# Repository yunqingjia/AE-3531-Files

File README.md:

# AE-3531-Files
Class project for the controls analysis course at Georgia Tech.

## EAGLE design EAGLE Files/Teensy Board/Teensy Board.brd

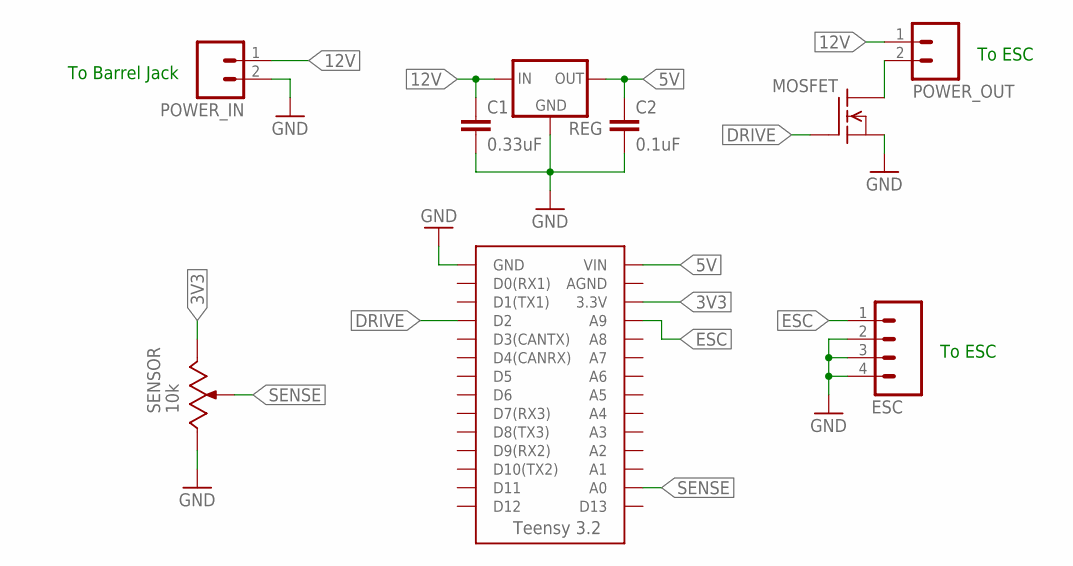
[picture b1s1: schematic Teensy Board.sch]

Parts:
C1: 0.33uF; 0805
C2: 0.1uF; 0805
ESC: M04; 1X04
MOSFET: SI2312; SOT-23
POWER_IN: M02; 1X02
POWER_OUT: M02; 1X02
REG: L78L; SOT-89
SENSOR: 10k; SV03A
U$2: TEENSY_3.2_SIMPLE

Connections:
3V3: SENSOR.1 (E), U$2.3.3V
5V: C2.1, REG.1 (OUT), U$2.VIN
12V: C1.1, POWER_IN.1, POWER_OUT.1, REG.3 (IN)
DRIVE: MOSFET.1 (G), U$2.D2
ESC: ESC.1, U$2.A9
GND: C1.2, C2.2, ESC.2, ESC.3, ESC.4, MOSFET.2 (S), POWER_IN.2, REG.2 (GND), REG.2.1 (GND), REG.2.2 (GND), SENSOR.3 (A), U$2.GND
unnamed: MOSFET.3 (D), POWER_OUT.2
SENSE: SENSOR.2 (S), SENSOR.2.1 (S), U$2.A0

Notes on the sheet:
To Barrel Jack
To ESC

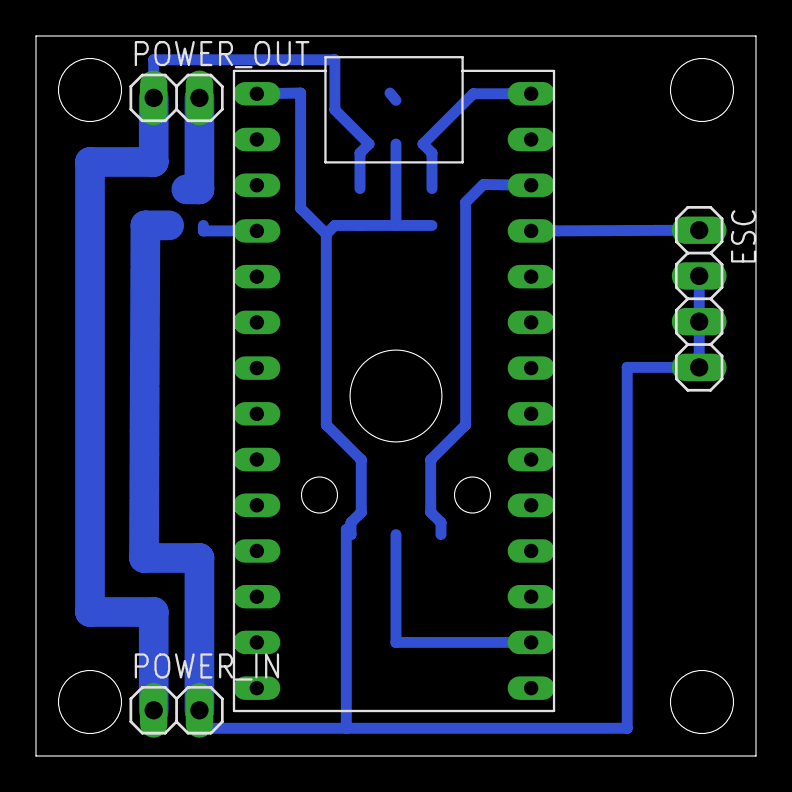
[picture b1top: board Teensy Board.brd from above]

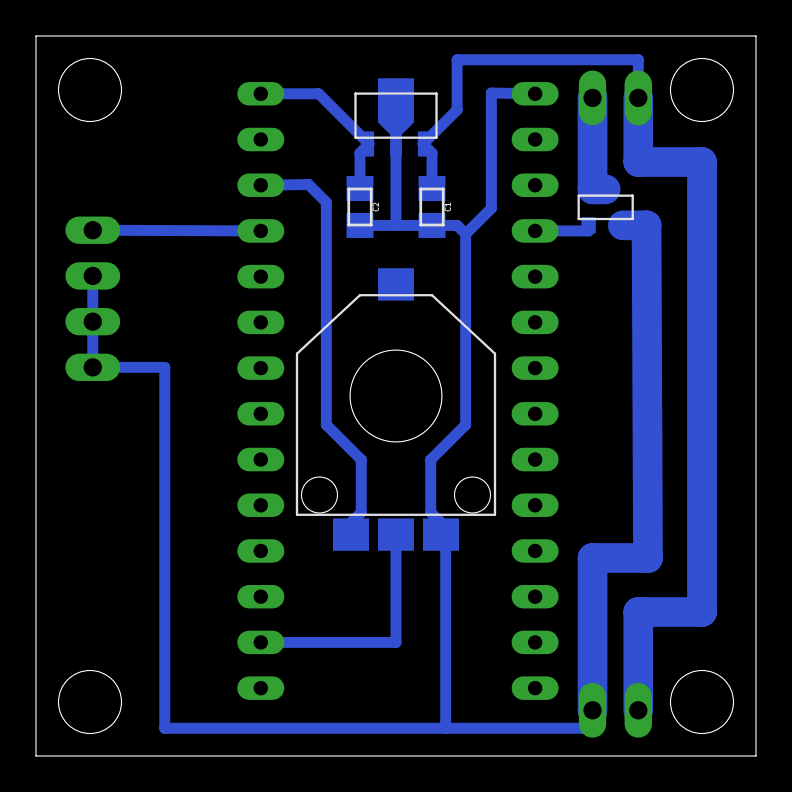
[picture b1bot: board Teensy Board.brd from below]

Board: 2 copper layers, 40.0 x 40.0 mm, 9 parts (5 on the bottom side), 8 nets.

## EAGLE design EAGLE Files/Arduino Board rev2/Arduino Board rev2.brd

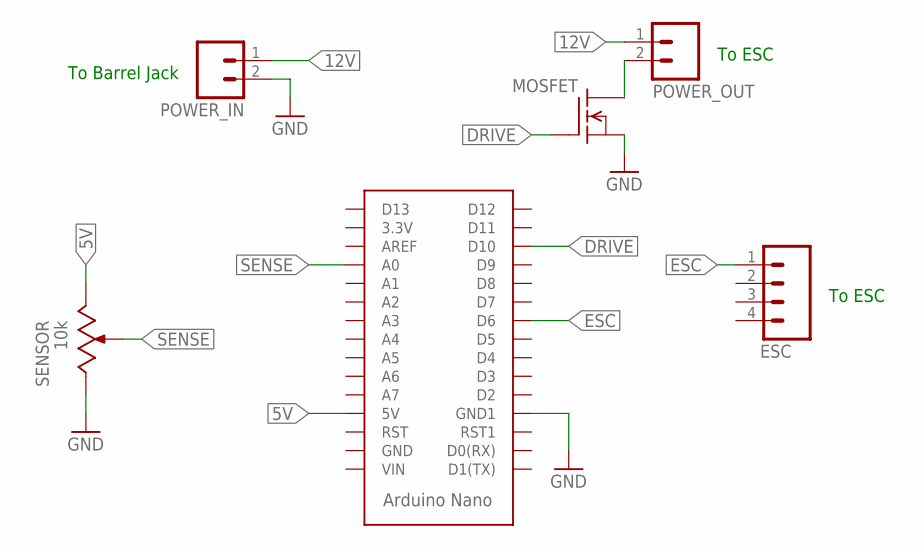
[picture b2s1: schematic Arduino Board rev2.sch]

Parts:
ESC: M04; 1X04
MOSFET: SI2312; SOT-23
POWER_IN: M02; 1X02
POWER_OUT: M02; 1X02
SENSOR: 10k; SV03A
U$1: ARDUINO_NANO

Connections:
5V: SENSOR.3 (A), U$1.5V
12V: POWER_IN.1, POWER_OUT.1
DRIVE: MOSFET.1 (G), U$1.D10
ESC: ESC.1, U$1.D6
GND: MOSFET.2 (S), POWER_IN.2, SENSOR.1 (E), U$1.GND1
unnamed: MOSFET.3 (D), POWER_OUT.2
SENSE: SENSOR.2 (S), SENSOR.2.1 (S), U$1.A0

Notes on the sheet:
To Barrel Jack
To ESC

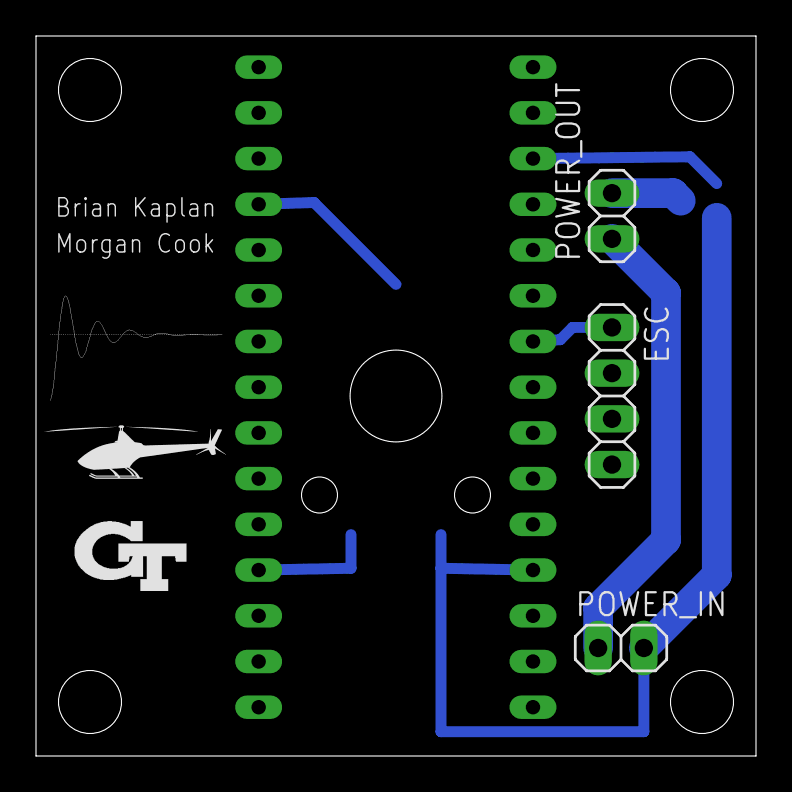
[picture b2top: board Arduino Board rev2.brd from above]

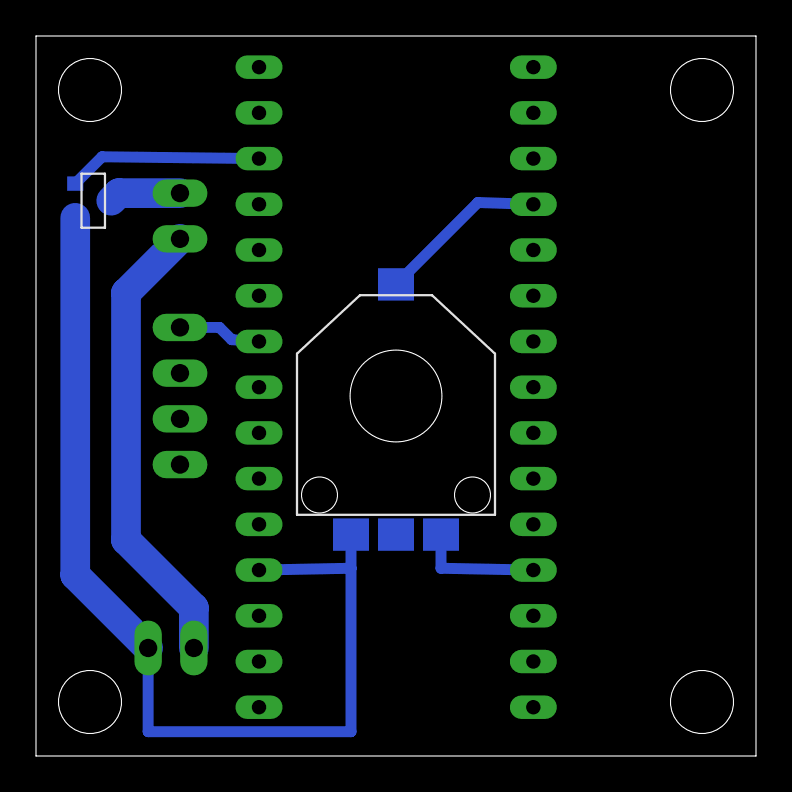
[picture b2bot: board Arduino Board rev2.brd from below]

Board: 2 copper layers, 40.0 x 40.0 mm, 6 parts (2 on the bottom side), 7 nets.

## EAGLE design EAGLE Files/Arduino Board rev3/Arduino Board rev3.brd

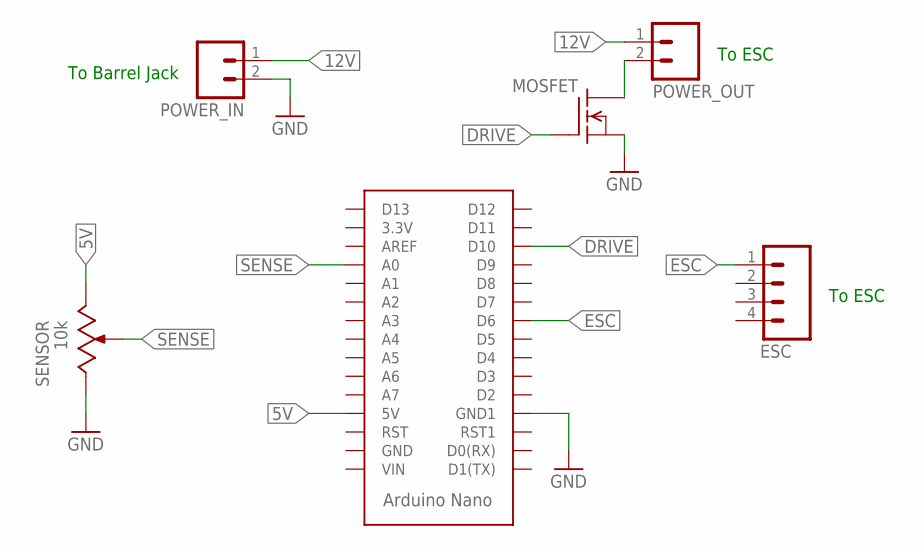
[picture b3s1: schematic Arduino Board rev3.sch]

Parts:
ARDUINO_NANO: ARDUINO_NANO
ESC: M04; 1X04
MOSFET: N-CHANNEL_MOSFETGENERIC; TO-220-SINK
POWER_IN: M02; 1X02
POWER_OUT: M02; 1X02
SENSOR: 10k; SV03A

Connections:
5V: ARDUINO_NANO.5V, SENSOR.3 (A)
12V: POWER_IN.1, POWER_OUT.1
DRIVE: ARDUINO_NANO.D10, MOSFET.1 (G)
ESC: ARDUINO_NANO.D6, ESC.1
GND: ARDUINO_NANO.GND1, MOSFET.3 (S), POWER_IN.2, SENSOR.1 (E)
unnamed: MOSFET.2 (D), POWER_OUT.2
SENSE: ARDUINO_NANO.A0, SENSOR.2 (S), SENSOR.2.1 (S)

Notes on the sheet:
To Barrel Jack
To ESC

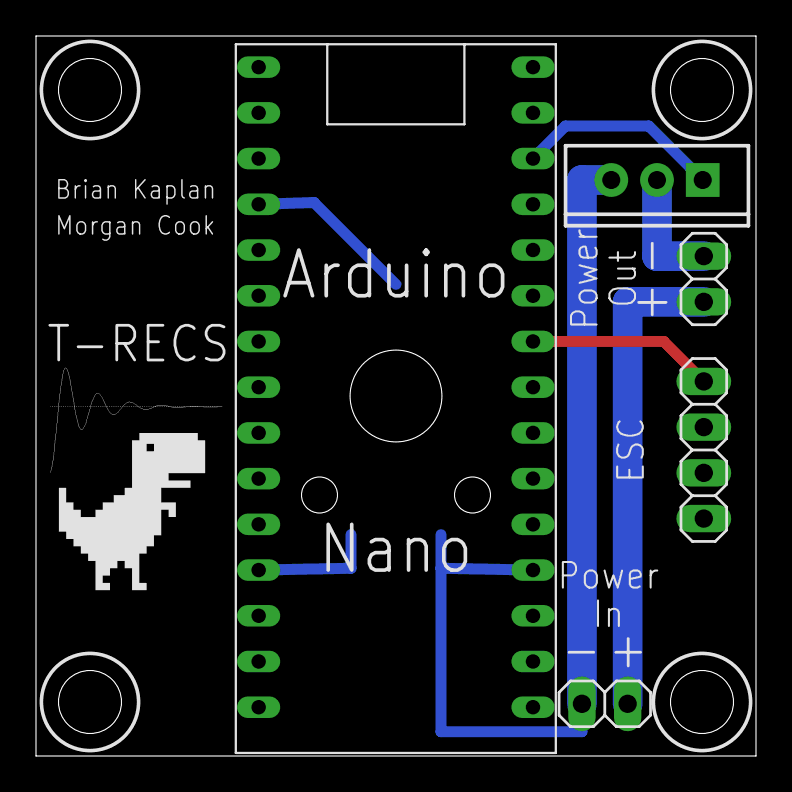
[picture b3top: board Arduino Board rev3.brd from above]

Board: 2 copper layers, 40.0 x 40.0 mm, 6 parts (1 on the bottom side), 7 nets.

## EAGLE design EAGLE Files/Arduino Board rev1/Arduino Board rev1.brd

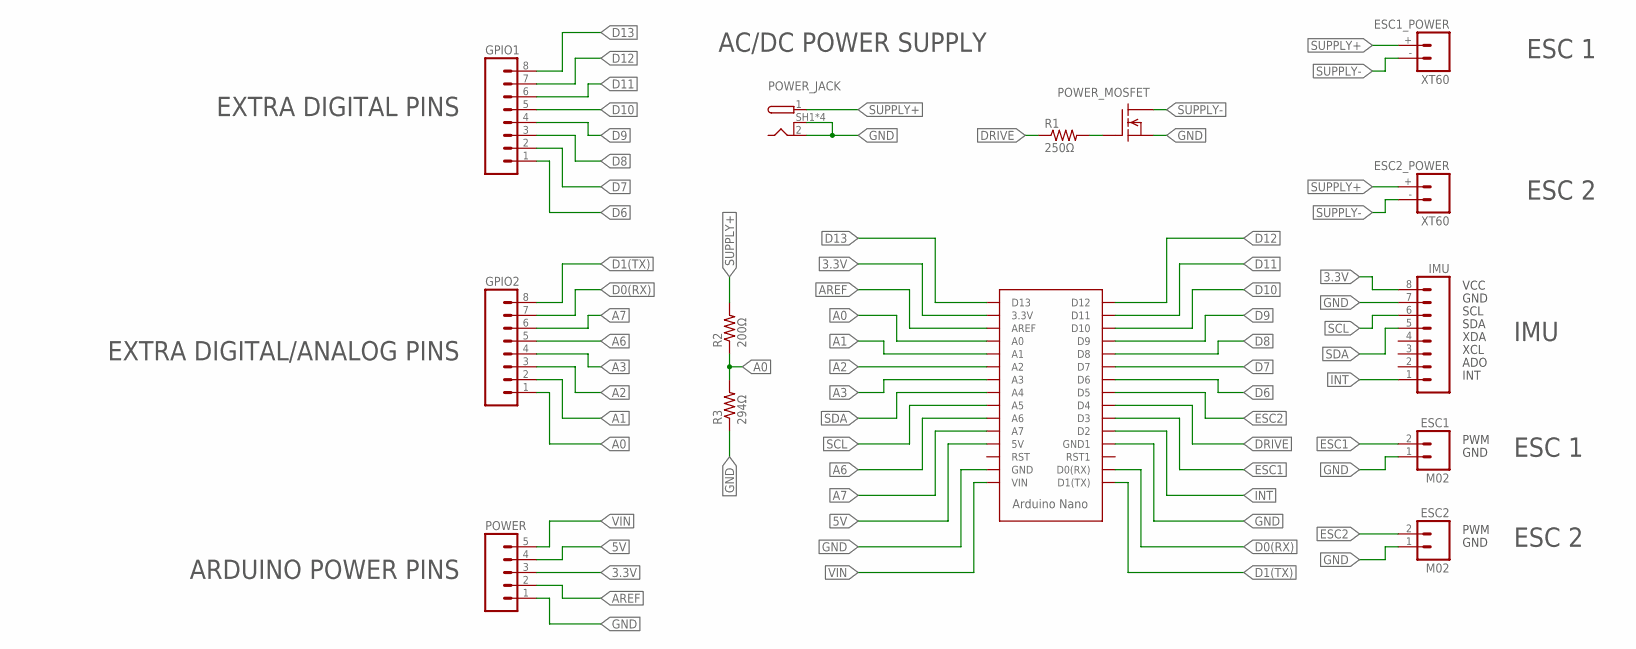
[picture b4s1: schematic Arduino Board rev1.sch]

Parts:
ESC1, ESC2: M02; 1X02
ESC1_POWER, ESC2_POWER: XT60
GPIO1, GPIO2: M08; 1X08
IMU: M08; 1X08
POWER: M05; 1X05
POWER_JACK: PJ-082BH
POWER_MOSFET: N-CHANNEL_MOSFETGENERIC; TO-220-SINK
R1: 250Ω; AXIAL-0.4
R2: 200Ω; AXIAL-0.4
R3: 294Ω; AXIAL-0.4
U$1: ARDUINO_NANO

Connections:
3.3V: IMU.8, POWER.3, U$1.3.3V
5V: POWER.4, U$1.5V
A0: GPIO2.1, R2.P$1 (1), R3.P$2 (2), U$1.A0
A1: GPIO2.2, U$1.A1
A2: GPIO2.3, U$1.A2
A3: GPIO2.4, U$1.A3
A6: GPIO2.5, U$1.A6
A7: GPIO2.6, U$1.A7
AREF: POWER.2, U$1.AREF
D0(RX): GPIO2.7, U$1.D0(RX)
D1(TX): GPIO2.8, U$1.D1(TX)
D6: GPIO1.1, U$1.D6
D7: GPIO1.2, U$1.D7
D8: GPIO1.3, U$1.D8
D9: GPIO1.4, U$1.D9
D10: GPIO1.5, U$1.D10
D11: GPIO1.6, U$1.D11
D12: GPIO1.7, U$1.D12
D13: GPIO1.8, U$1.D13
DRIVE: R1.P$1 (1), U$1.D4
ESC1: ESC1.2, U$1.D3
ESC2: ESC2.2, U$1.D5
GND: ESC1.1, ESC2.1, IMU.7, POWER.1, POWER_JACK.2 (GND), POWER_JACK.SH1 (SHIELD), POWER_JACK.SH2 (SHIELD), POWER_JACK.SH3 (SHIELD), POWER_JACK.SH4 (SHIELD), POWER_MOSFET.3 (S), R3.P$1 (1), U$1.GND, U$1.GND1
INT: IMU.1, U$1.D2
unnamed: POWER_MOSFET.1 (G), R1.P$2 (2)
SCL: IMU.6, U$1.A5
SDA: IMU.5, U$1.A4
SUPPLY+: ESC1_POWER.+ (2), ESC2_POWER.+ (2), POWER_JACK.1 (PWR), R2.P$2 (2)
SUPPLY-: ESC1_POWER.- (1), ESC2_POWER.- (1), POWER_MOSFET.2 (D)
VIN: POWER.5, U$1.VIN

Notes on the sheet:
VCC
GND
SCL
SDA
XDA
XCL
ADO
INT
PWM
ESC 1
ESC 2
IMU
AC/DC POWER SUPPLY
EXTRA DIGITAL PINS
EXTRA DIGITAL/ANALOG PINS
ARDUINO POWER PINS

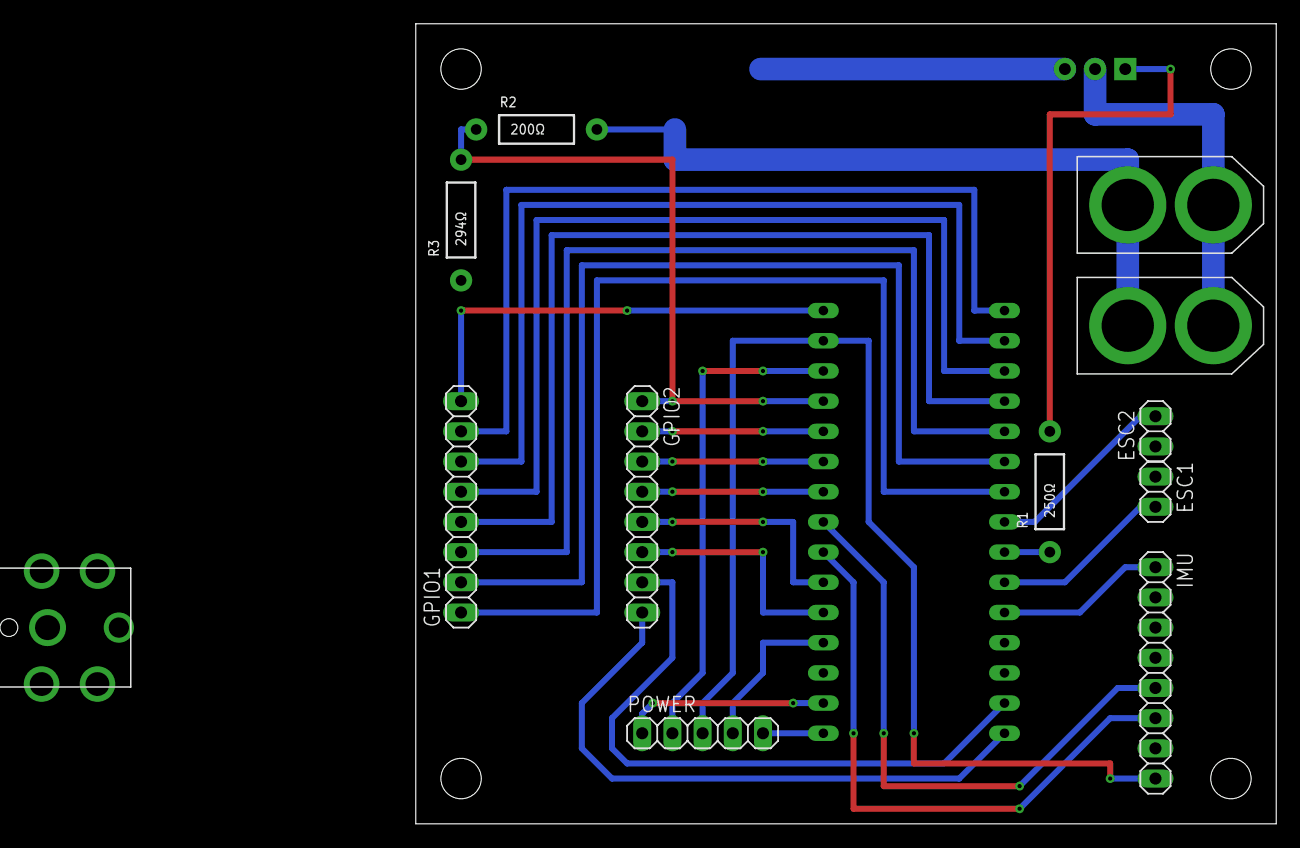
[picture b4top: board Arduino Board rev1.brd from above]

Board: 2 copper layers, 72.4 x 67.3 mm, 14 parts (1 on the bottom side), 30 nets.

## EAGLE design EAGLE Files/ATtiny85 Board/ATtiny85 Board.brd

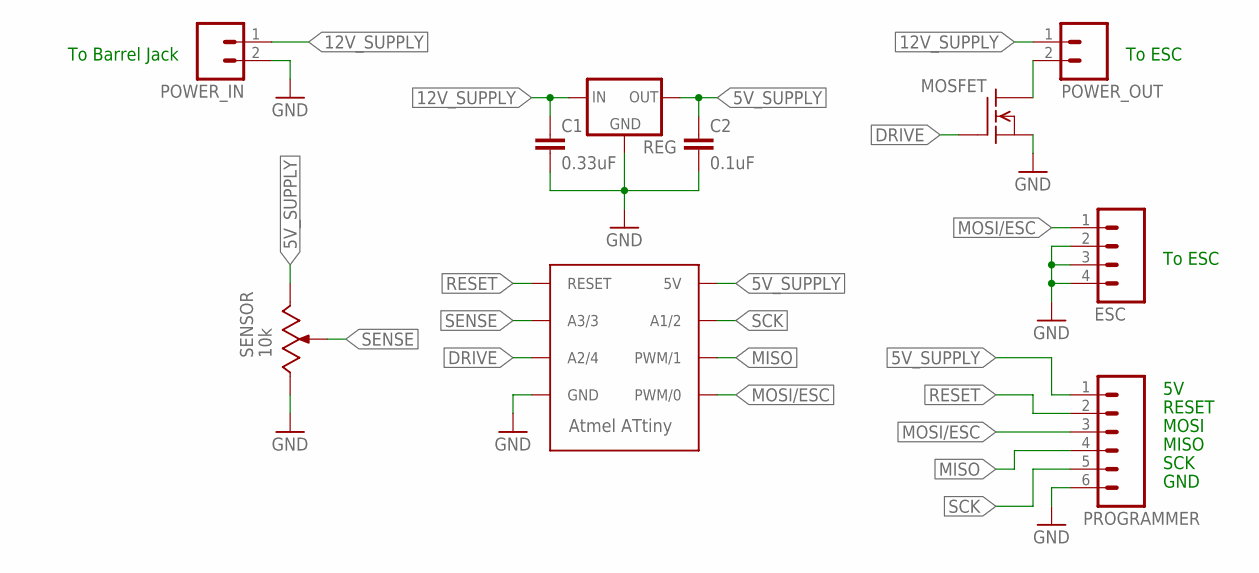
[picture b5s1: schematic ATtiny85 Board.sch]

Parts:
C1: 0.33uF; 0805
C2: 0.1uF; 0805
ESC: M04; 1X04
MOSFET: SI2312; SOT-23
POWER_IN: M02; 1X02
POWER_OUT: M02; 1X02
PROGRAMMER: M06; 1X06
REG: L78L; SOT-89
SENSOR: 10k; SV03A
U$1: ATTINY; 8S2

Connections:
5V_SUPPLY: C2.1, PROGRAMMER.1, REG.1 (OUT), SENSOR.1 (E), U$1.8 (5V)
12V_SUPPLY: C1.1, POWER_IN.1, POWER_OUT.1, REG.3 (IN)
DRIVE: MOSFET.1 (G), U$1.3 (A2/4)
GND: C1.2, C2.2, ESC.2, ESC.3, ESC.4, MOSFET.2 (S), POWER_IN.2, PROGRAMMER.6, REG.2 (GND), REG.2.1 (GND), REG.2.2 (GND), SENSOR.3 (A), U$1.4 (GND)
MISO: PROGRAMMER.4, U$1.6 (PWM/1)
MOSI/ESC: ESC.1, PROGRAMMER.3, U$1.5 (PWM/0)
unnamed: MOSFET.3 (D), POWER_OUT.2
RESET: PROGRAMMER.2, U$1.1 (RESET)
SCK: PROGRAMMER.5, U$1.7 (A1/2)
SENSE: SENSOR.2 (S), SENSOR.2.1 (S), U$1.2 (A3/3)

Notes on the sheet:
RESET
MOSI
MISO
SCK
To Barrel Jack
To ESC
GND

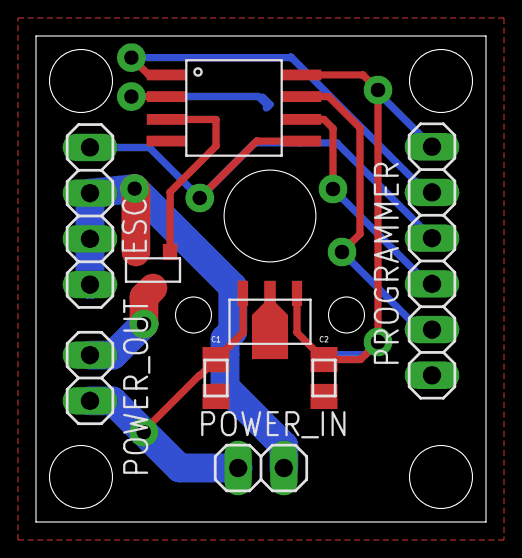
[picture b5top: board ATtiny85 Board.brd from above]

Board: 2 copper layers, 25.0 x 27.0 mm, 10 parts (1 on the bottom side), 10 nets.
